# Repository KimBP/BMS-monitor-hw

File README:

This repository contains a Kicad project defining the HW for the
bms-monitor project.

Version v2.0 is a prototype made for an esp32s3_devkitc with 9 or 10  modules 
between the two pin rows.

The display to use is a 3.5" TFT LCD shield based on a ILI9488 controller
with SPI.
Furthermore the display has an xpt2046 touch controller. Also SPI

TO CHANGE in next version:

- Diodes to make power possible both via NMEA connector and a separate power
  supply at the same time

- Buffer on 5V to 3V pins (CAN buffer to ESP32)

- Pullup on touch MISO

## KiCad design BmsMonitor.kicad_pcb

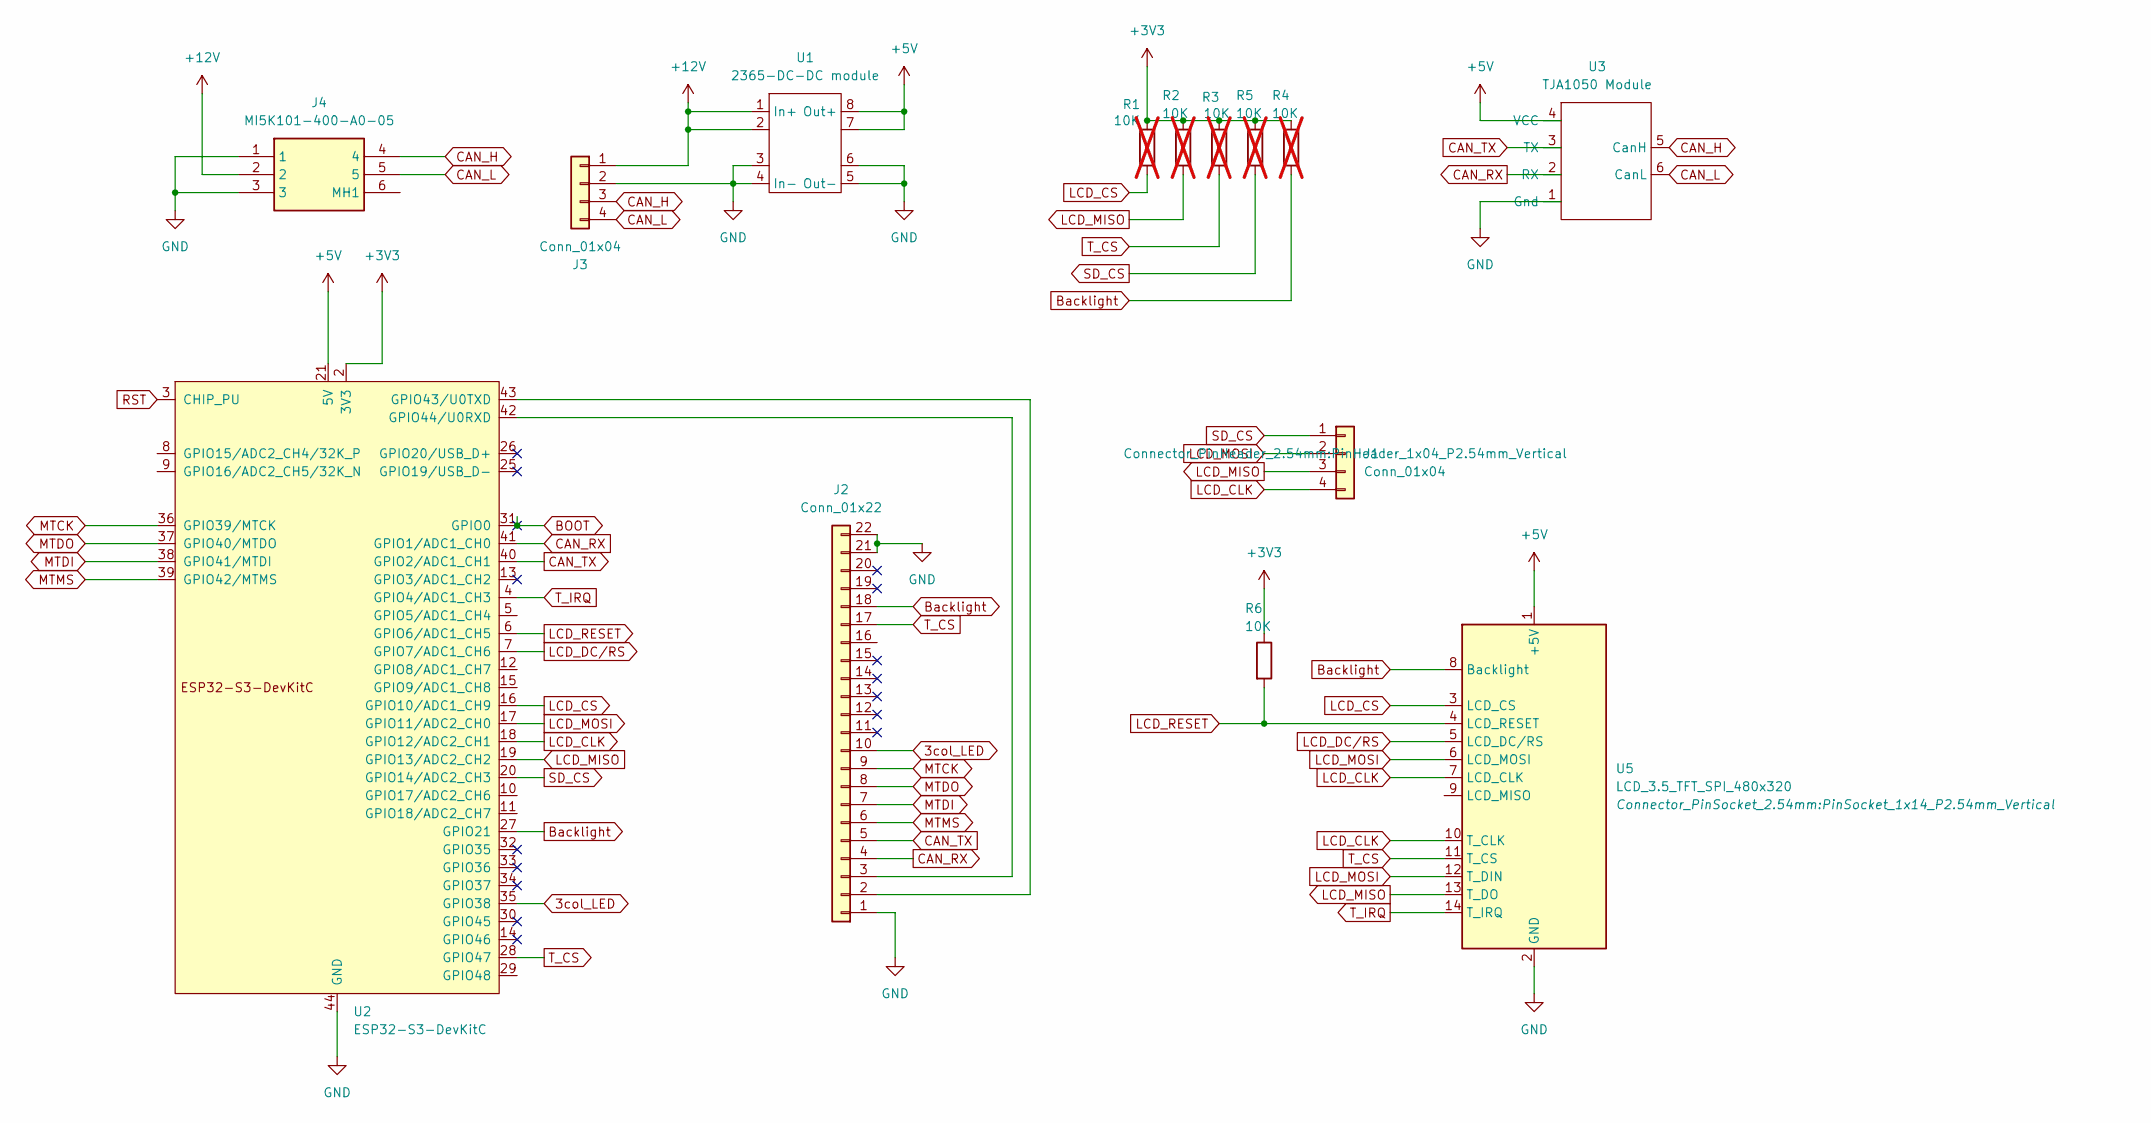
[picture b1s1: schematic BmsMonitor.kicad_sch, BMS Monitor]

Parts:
J1: Conn_01x04; PinHeader_1x04_P2.54mm_Vertical
J2: Conn_01x22; PinHeader_1x22_P2.54mm_Vertical
J3: Conn_01x04; TerminalBlock_bornier-4_P5.08mm
J4: MI5K101-400-A0-05; MI5K101400A005; Manufacturer_Part_Number MI5K101-400-A0-05
R1, R2, R3, R4, R5: 10K; R_Box_L8.4mm_W2.5mm_P5.08mm; not fitted
R6: 10K; R_Box_L8.4mm_W2.5mm_P5.08mm
U1: 2365-DC-DC module; DC-DC-2365-Module
U2: ESP32-S3-DevKitC
U3: TJA1050 Module; CAN_Transceiver_Module
U5: LCD_3.5_TFT_SPI_480x320; PinSocket_1x14_P2.54mm_Vertical

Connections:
3col_LED: J2.10, U2.35 (GPIO38)
+3V3: R1.1, R2.1, R3.1, R4.1, R5.1, R6.1, U2.1 (3V3), U2.2 (3V3)
+5V: U1.7, U1.8 (Out+), U2.21 (5V), U3.4 (VCC), U5.1 (+5V)
+12V: J3.1, J4.2, U1.1 (In+), U1.2
BOOT: U2.31 (GPIO0)
Backlight: J2.18, R4.2, U2.27 (GPIO21), U5.8 (Backlight)
CAN_H: J3.3, J4.4, U3.5 (CanH)
CAN_L: J3.4, J4.5, U3.6 (CanL)
CAN_RX: J2.4, U2.41 (GPIO1/ADC1_CH0), U3.2 (RX)
CAN_TX: J2.5, U2.40 (GPIO2/ADC1_CH1), U3.3 (TX)
GND: J2.1, J2.21, J2.22, J3.2, J4.1, J4.3, U1.3, U1.4 (In-), U1.5 (Out-), U1.6, U2.22 (GND), U2.23 (GND), U2.24 (GND), U2.44 (GND), U3.1 (Gnd), U5.2 (GND)
LCD_CLK: J1.4, U2.18 (GPIO12/ADC2_CH1), U5.7 (LCD_CLK), U5.10 (T_CLK)
LCD_CS: R1.2, U2.16 (GPIO10/ADC1_CH9), U5.3 (LCD_CS)
LCD_DC/RS: U2.7 (GPIO7/ADC1_CH6), U5.5 (LCD_DC/RS)
LCD_MISO: J1.3, R2.2, U2.19 (GPIO13/ADC2_CH2), U5.13 (T_DO)
LCD_MOSI: J1.2, U2.17 (GPIO11/ADC2_CH0), U5.6 (LCD_MOSI), U5.12 (T_DIN)
LCD_RESET: R6.2, U2.6 (GPIO6/ADC1_CH5), U5.4 (LCD_RESET)
MTCK: J2.9, U2.36 (GPIO39/MTCK)
MTDI: J2.7, U2.38 (GPIO41/MTDI)
MTDO: J2.8, U2.37 (GPIO40/MTDO)
MTMS: J2.6, U2.39 (GPIO42/MTMS)
unnamed: J2.2, U2.43 (GPIO43/U0TXD)
unnamed: J2.3, U2.42 (GPIO44/U0RXD)
RST: U2.3 (CHIP_PU)
SD_CS: J1.1, R5.2, U2.20 (GPIO14/ADC2_CH3)
T_CS: J2.17, R3.2, U2.28 (GPIO47), U5.11 (T_CS)
T_IRQ: U2.4 (GPIO4/ADC1_CH3), U5.14 (T_IRQ)

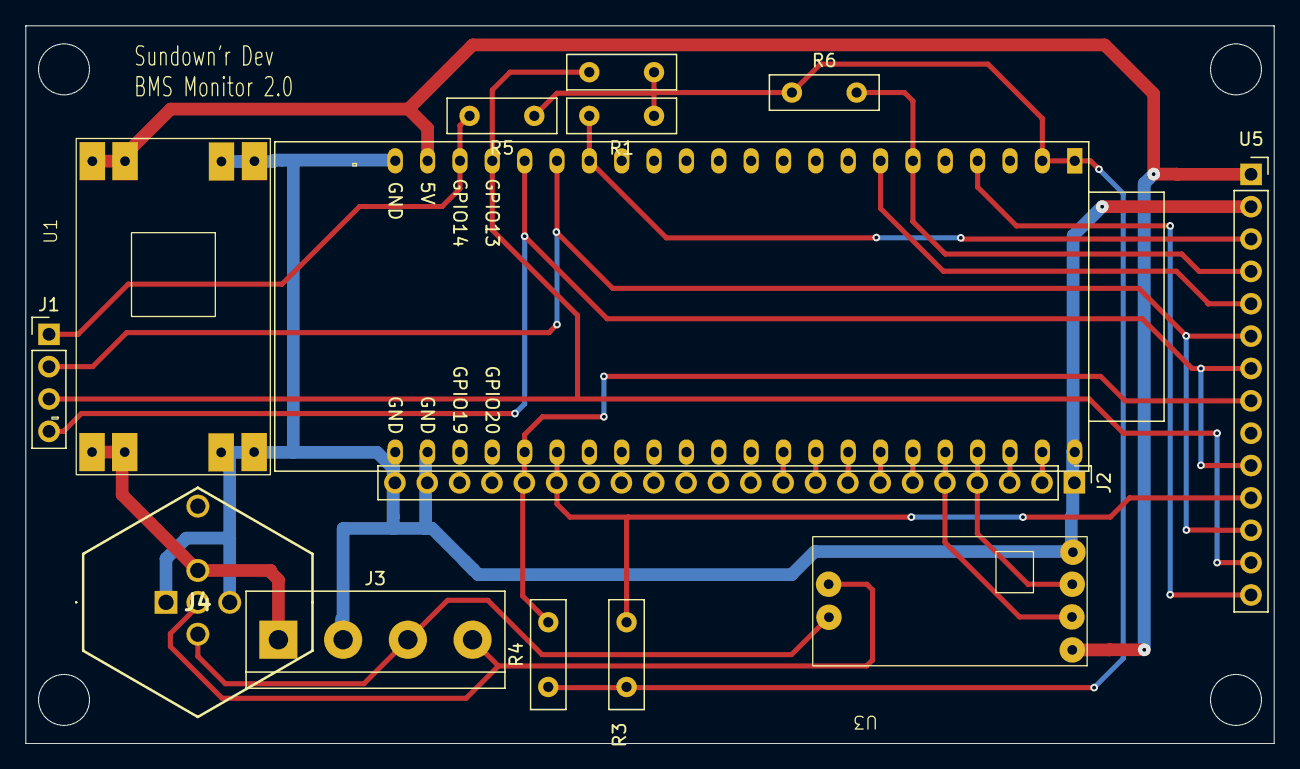
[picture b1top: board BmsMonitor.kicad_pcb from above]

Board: 2 copper layers, 98.0 x 56.3 mm, 14 parts (0 on the bottom side), 25 nets.

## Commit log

2024-04-24 First version - using modules
2024-04-24 Gerber for version 1.0
2024-10-08 README added in first version
2024-10-19 gitignore added
2024-10-19 BmsMonitor Ver 2.0
    Changed to work with Display having a SPI variant of ILI9488
    as well as a XPT2046 touch controller.
    The display in question is this 3.5" display:
    https://www.aliexpress.com/item/33057812377.html
2024-10-19 Production files for V2.0 of the BMS Monitor
2024-12-09 Use common SPI for both display and touch.
    Added M12 connector for possible power and CAN
2024-12-09 Production files for V2.0 (second version) of the BMS monitor
2025-04-13 README: V2.0 info. TODO added
